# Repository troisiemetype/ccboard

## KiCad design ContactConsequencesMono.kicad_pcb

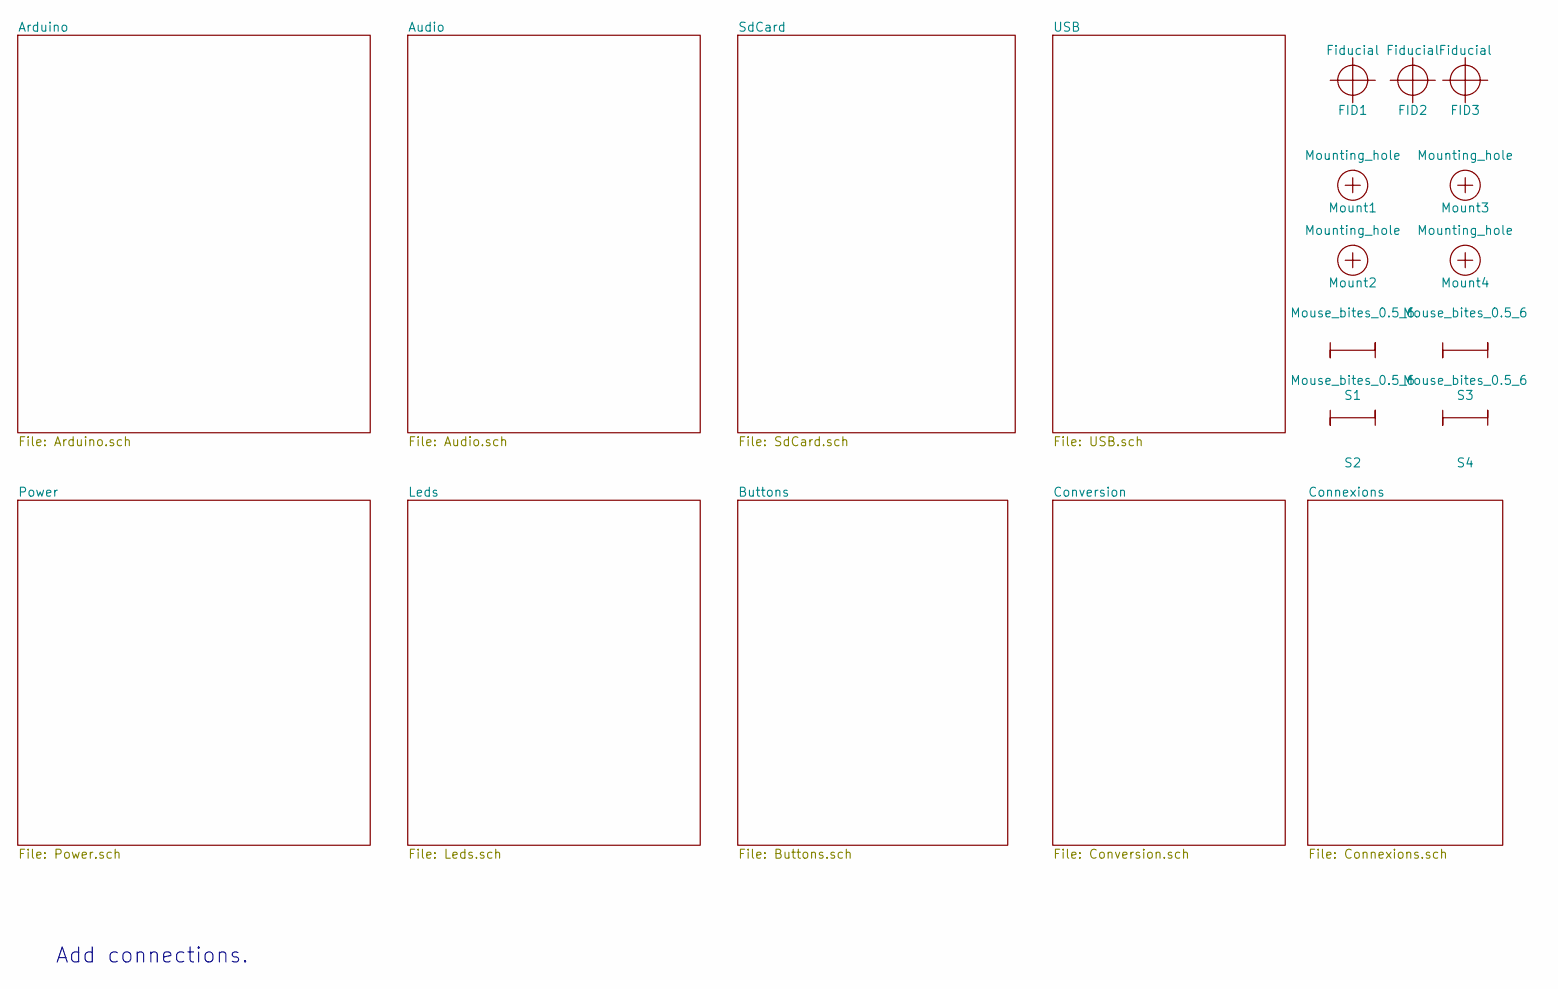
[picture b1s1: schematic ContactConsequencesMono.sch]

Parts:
FID1, FID2, FID3: Fiducial; Fiducial_1mm_Dia_2.54mm_Outer_CopperTop
Mount1, Mount2, Mount3, Mount4: Mounting_hole; MountingHole_3.2mm_M3
S1, S2, S3, S4: Mouse_bites_0.5_6

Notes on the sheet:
Add connections.

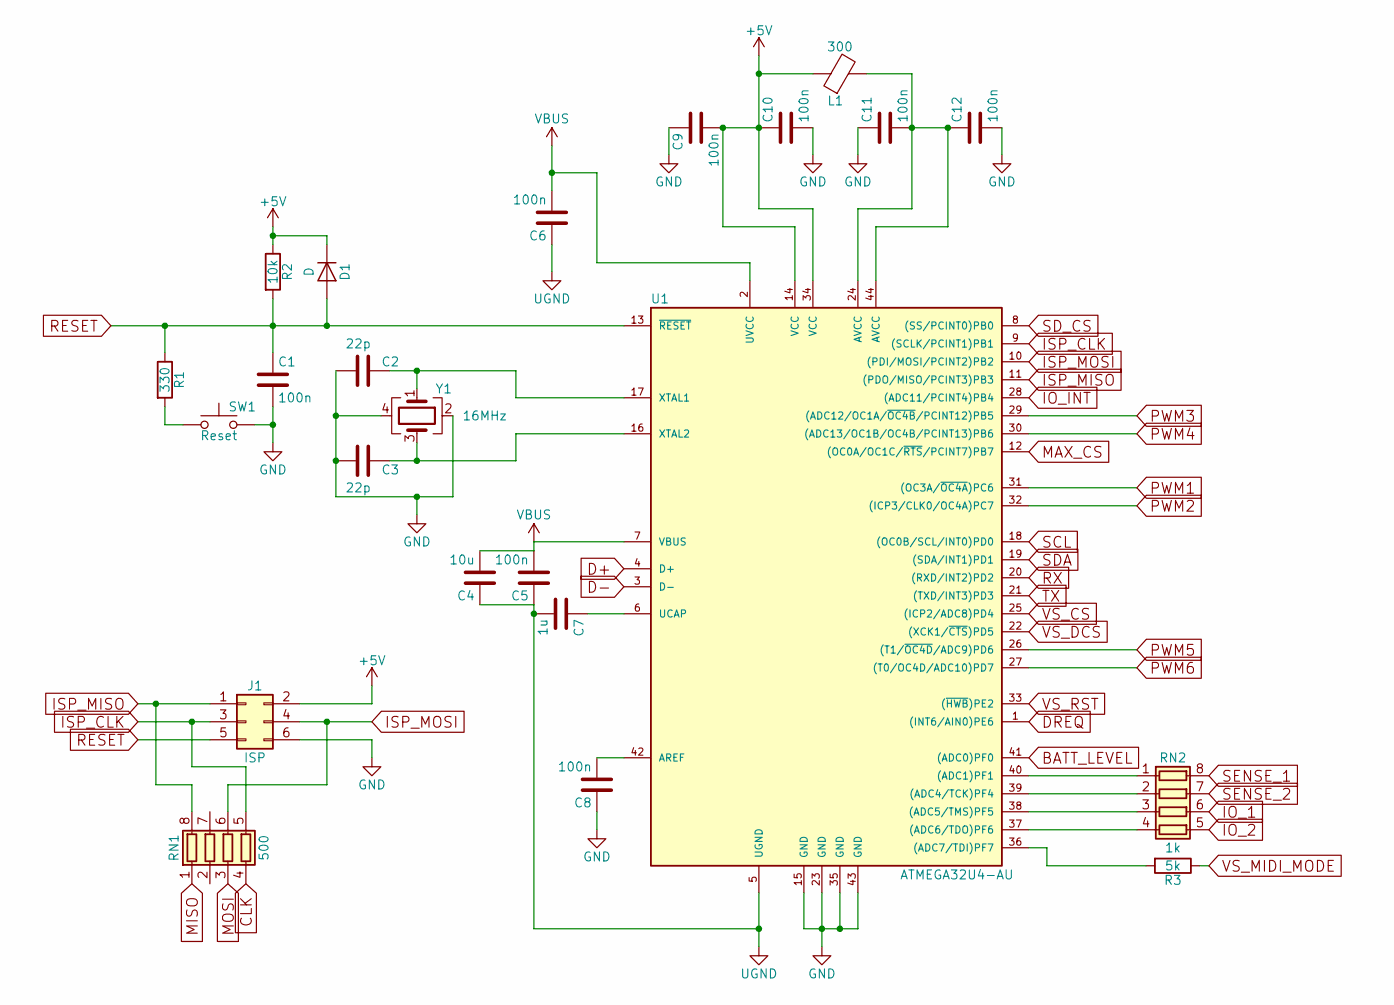
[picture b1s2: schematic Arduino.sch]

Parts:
C1, C5, C6, C8, C9, C10, C11, C12: 100n; C_0603
C2, C3: 22p; C_0603
C4: 10u; C_0603
C7: 1u; C_0603
D1: D; D_1206
J1: ISP; Pin_Header_Straight_2x03_Pitch2.54mm
L1: 300; L_0603
R1: 330; R_0603
R2: 10k; R_0603
R3: 5k; R_0603
RN1: 500; R_Array_Concave_4x0603
RN2: 1k; R_Array_Concave_4x0603
SW1: Reset; SW_Tactile_SKHH_Angled
U1: ATMEGA32U4-AU; TQFP-44_10x10mm_Pitch0.8mm
Y1: 16MHz; Crystal_SMD_5032-4pin_5.0x3.2mm

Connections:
+5V: C9.2, C10.1, D1.1 (K), J1.2, L1.1, R2.1, U1.14 (VCC), U1.34 (VCC); also elsewhere on the board
BATT_LEVEL: U1.41 ((ADC0)PF0); also elsewhere on the board
CLK: RN1.4 (R4.1); also elsewhere on the board
D+: U1.4 (D+); also elsewhere on the board
D-: U1.3 (D-); also elsewhere on the board
DGND: C1.2, C2.2, C3.2, C8.1, C9.1, C10.2, C11.1, C12.2, J1.6, SW1.2, U1.15 (GND), U1.23 (GND), U1.35 (GND), U1.43 (GND), Y1.2, Y1.4; also elsewhere on the board
DREQ: U1.1 ((INT6/AIN0)PE6); also elsewhere on the board
IO_1: RN2.6 (R3.2); also elsewhere on the board
IO_2: RN2.5 (R4.2); also elsewhere on the board
IO_INT: U1.28 ((ADC11/PCINT4)PB4); also elsewhere on the board
ISP_CLK: J1.3, RN1.5 (R4.2), U1.9 ((SCLK/PCINT1)PB1)
ISP_MISO: J1.1, RN1.8 (R1.2), U1.11 ((PDO/MISO/PCINT3)PB3)
ISP_MOSI: J1.4, RN1.6 (R3.2), U1.10 ((PDI/MOSI/PCINT2)PB2)
MAX_CS: U1.12 ((OC0A/OC1C/~RTS~/PCINT7)PB7); also elsewhere on the board
MISO: RN1.1 (R1.1); also elsewhere on the board
MOSI: RN1.3 (R3.1); also elsewhere on the board
unnamed: C2.1, U1.17 (XTAL1), Y1.1
unnamed: C3.1, U1.16 (XTAL2), Y1.3
unnamed: C7.1, U1.6 (UCAP)
unnamed: C8.2, U1.42 (AREF)
unnamed: C11.2, C12.1, L1.2, U1.24 (AVCC), U1.44 (AVCC)
unnamed: R1.2, SW1.1
unnamed: R3.2, U1.36 ((ADC7/TDI)PF7)
unnamed: RN2.1 (R1.1), U1.40 ((ADC1)PF1)
unnamed: RN2.2 (R2.1), U1.39 ((ADC4/TCK)PF4)
unnamed: RN2.3 (R3.1), U1.38 ((ADC5/TMS)PF5)
unnamed: RN2.4 (R4.1), U1.37 ((ADC6/TDO)PF6)
PWM1: U1.31 ((OC3A/~OC4A~)PC6); also elsewhere on the board
PWM2: U1.32 ((ICP3/CLK0/OC4A)PC7); also elsewhere on the board
PWM3: U1.29 ((ADC12/OC1A/~OC4B~/PCINT12)PB5); also elsewhere on the board
PWM4: U1.30 ((ADC13/OC1B/OC4B/PCINT13)PB6); also elsewhere on the board
PWM5: U1.26 ((T1/~OC4D~/ADC9)PD6); also elsewhere on the board
PWM6: U1.27 ((T0/OC4D/ADC10)PD7); also elsewhere on the board
RESET: C1.1, D1.2 (A), J1.5, R1.1, R2.2, U1.13 (~RESET~)
RX: U1.20 ((RXD/INT2)PD2); also elsewhere on the board
SCL: U1.18 ((OC0B/SCL/INT0)PD0); also elsewhere on the board
SDA: U1.19 ((SDA/INT1)PD1); also elsewhere on the board
SD_CS: U1.8 ((SS/PCINT0)PB0); also elsewhere on the board
SENSE_1: RN2.8 (R1.2); also elsewhere on the board
SENSE_2: RN2.7 (R2.2); also elsewhere on the board
TX: U1.21 ((TXD/INT3)PD3); also elsewhere on the board
UGND: C4.1, C5.1, C6.1, C7.2, U1.5 (UGND); also elsewhere on the board
VBUS: C4.2, C5.2, C6.2, U1.2 (UVCC), U1.7 (VBUS); also elsewhere on the board
VS_CS: U1.25 ((ICP2/ADC8)PD4); also elsewhere on the board
VS_DCS: U1.22 ((XCK1/~CTS~)PD5); also elsewhere on the board
VS_MIDI_MODE: R3.1; also elsewhere on the board
VS_RST: U1.33 ((~HWB~)PE2); also elsewhere on the board

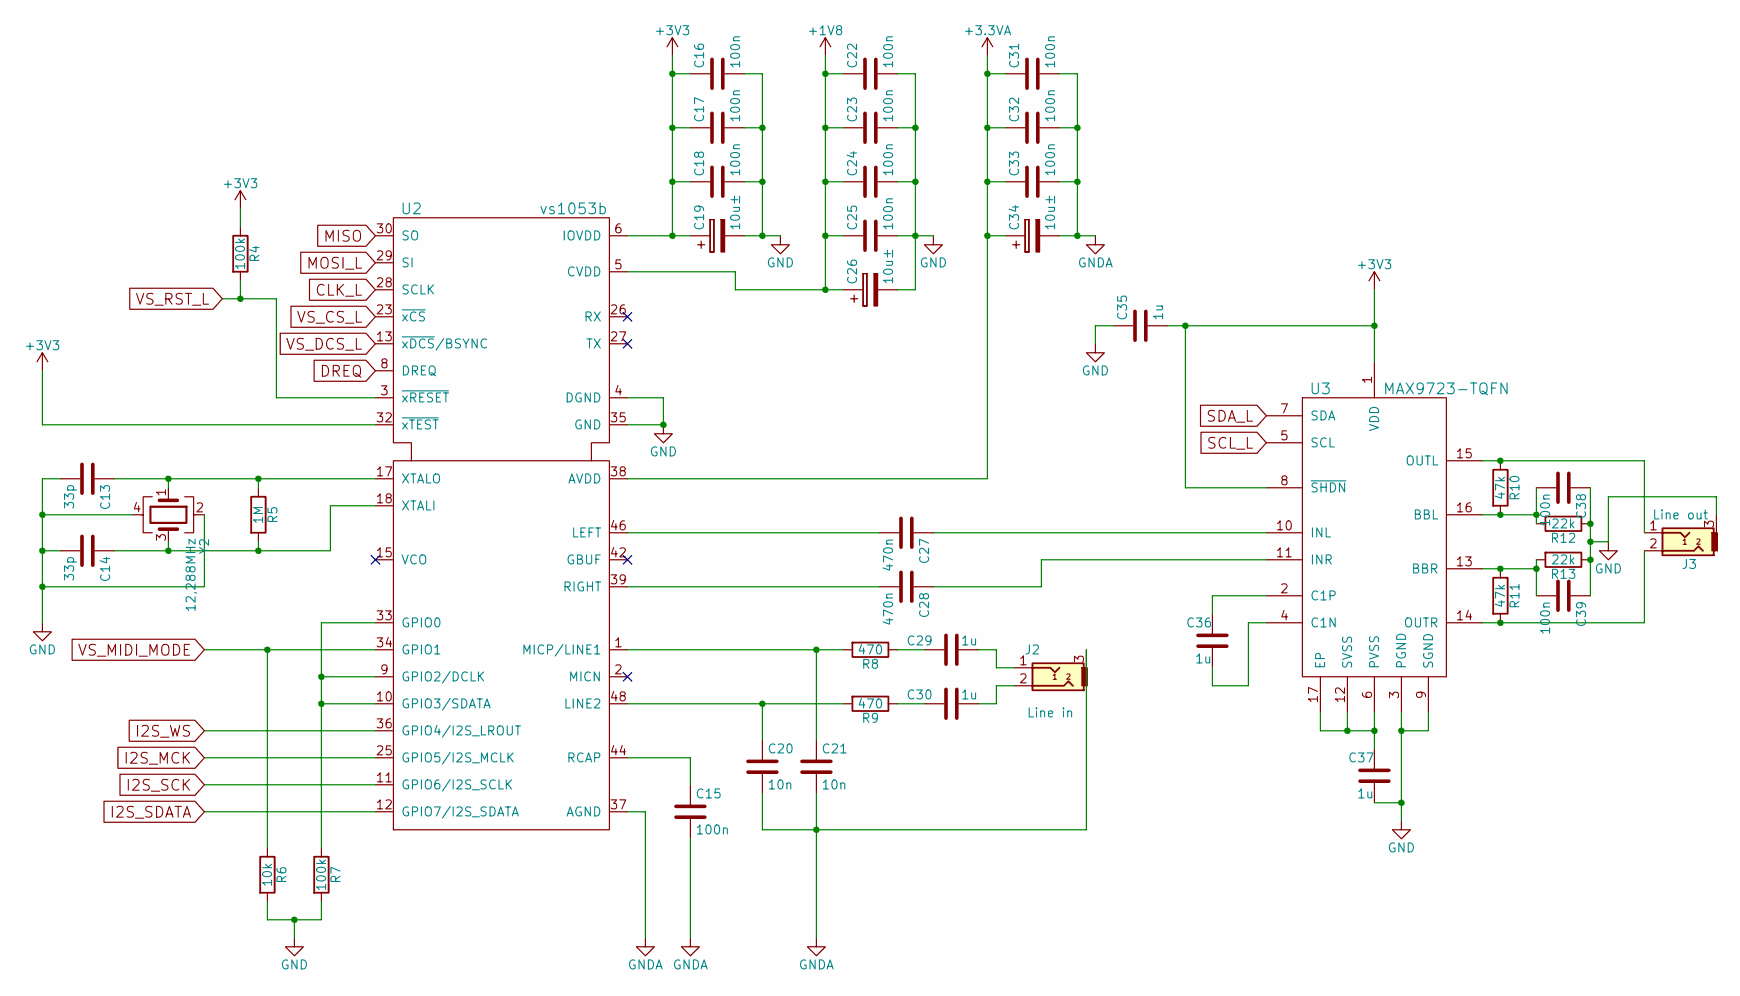
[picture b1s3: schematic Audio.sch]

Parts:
C13, C14: 33p; C_0603
C15, C16, C17, C18, C22, C23, C24, C25, C31, C32, C33, C38, C39: 100n; C_0603
C19, C26, C34: 10u±; CP_Tantalum_Case-A_EIA-3216-18_Reflow
C20, C21: 10n; C_0603
C27, C28: 470n; C_0603
C29, C30, C35, C36, C37: 1u; C_0603
J2: Line in; PJ320D_3.5mm_Jack
J3: Line out; PJ320D_3.5mm_Jack
R4, R7: 100k; R_0603
R5: 1M; R_0603
R6: 10k; R_0603
R8, R9: 470; R_0603
R10, R11: 47k; R_0603
R12, R13: 22k; R_0603
U2: vs1053b; LQFP-48_7x7mm_Pitch0.5mm
U3: MAX9723-TQFN; QFN-16-1EP_4x4mm_Pitch0.65mm
Y2: 12,288MHz; Crystal_SMD_5032-4pin_5.0x3.2mm

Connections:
+1V8: C22.1, C23.1, C24.1, C25.1, C26.1, U2.5 (CVDD), U2.7 (CVDD), U2.24 (CVDD), U2.31 (CVDD); also elsewhere on the board
+3.3VA: C31.1, C32.1, C33.1, C34.1, U2.38 (AVDD), U2.43 (AVDD), U2.45 (AVDD); also elsewhere on the board
AGND: C15.2, C20.2, C21.2, C31.2, C32.2, C33.2, C34.2, J2.3, U2.37 (AGND), U2.40 (AGND), U2.41 (AGND), U2.47 (AGND); also elsewhere on the board
CLK_L: U2.28 (SCLK); also elsewhere on the board
DGND: C13.2, C14.2, C16.2, C17.2, C18.2, C19.2, C22.2, C23.2, C24.2, C25.2, C26.2, C35.1, C37.2, C38.1, C39.1, J3.3, R6.2, R7.2, R12.1, R13.1, U2.4 (DGND), U2.16 (DGND), U2.20 (DGND), U2.21 (DGND), U2.22 (DGND), U2.35 (GND), U3.3 (PGND), U3.9 (SGND), Y2.2, Y2.4; also elsewhere on the board
DREQ: U2.8 (DREQ); also elsewhere on the board
I2S_MCK: U2.25 (GPIO5/I2S_MCLK); also elsewhere on the board
I2S_SCK: U2.11 (GPIO6/I2S_SCLK); also elsewhere on the board
I2S_SDATA: U2.12 (GPIO7/I2S_SDATA); also elsewhere on the board
I2S_WS: U2.36 (GPIO4/I2S_LROUT); also elsewhere on the board
MISO: U2.30 (SO); also elsewhere on the board
MOSI_L: U2.29 (SI); also elsewhere on the board
unnamed: C13.1, R5.1, U2.17 (XTALO), Y2.1
unnamed: C14.1, R5.2, U2.18 (XTALI), Y2.3
unnamed: C15.1, U2.44 (RCAP)
unnamed: C20.1, R9.2, U2.48 (LINE2)
unnamed: C21.1, R8.2, U2.1 (MICP/LINE1)
unnamed: C27.1, U3.10 (INL)
unnamed: C27.2, U2.46 (LEFT)
unnamed: C28.1, U3.11 (INR)
unnamed: C28.2, U2.39 (RIGHT)
unnamed: C29.1, R8.1
unnamed: C29.2, J2.1
unnamed: C30.1, R9.1
unnamed: C30.2, J2.2
unnamed: C36.1, U3.2 (C1P)
unnamed: C36.2, U3.4 (C1N)
unnamed: C37.1, U3.6 (PVSS), U3.12 (SVSS), U3.17 (EP)
unnamed: C38.2, R10.2, R12.2, U3.16 (BBL)
unnamed: C39.2, R11.1, R13.2, U3.13 (BBR)
unnamed: J3.1, R10.1, U3.15 (OUTL)
unnamed: J3.2, R11.2, U3.14 (OUTR)
unnamed: R7.1, U2.9 (GPIO2/DCLK), U2.10 (GPIO3/SDATA), U2.33 (GPIO0)
SCL_L: U3.5 (SCL); also elsewhere on the board
SDA_L: U3.7 (SDA); also elsewhere on the board
VS_CS_L: U2.23 (~xCS); also elsewhere on the board
VS_DCS_L: U2.13 (~xDCS~/BSYNC); also elsewhere on the board
VS_MIDI_MODE: R6.1, U2.34 (GPIO1); also elsewhere on the board
VS_RST_L: R4.2, U2.3 (~xRESET); also elsewhere on the board

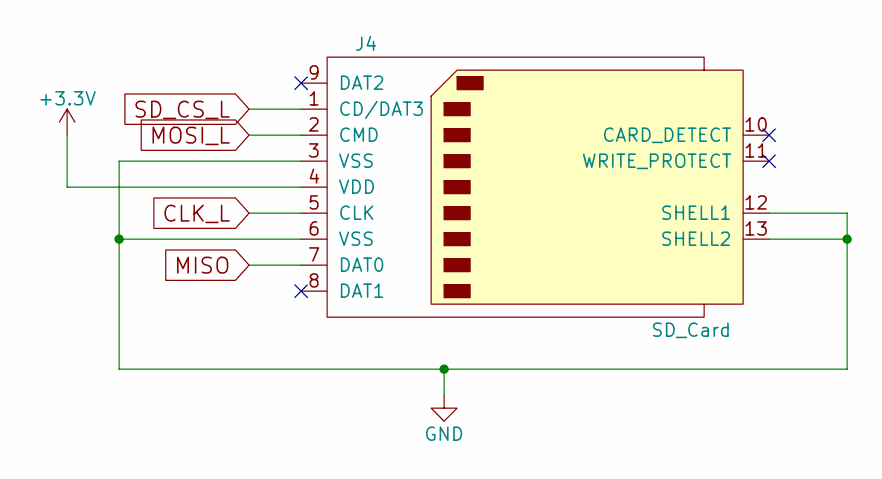
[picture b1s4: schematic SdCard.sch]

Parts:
J4: SD_Card; SD_Card_Receptacle

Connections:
CLK_L: J4.5 (CLK); also elsewhere on the board
DGND: J4.3 (VSS), J4.6 (VSS), J4.12 (SHELL1), J4.13 (SHELL2); also elsewhere on the board
MISO: J4.7 (DAT0); also elsewhere on the board
MOSI_L: J4.2 (CMD); also elsewhere on the board
SD_CS_L: J4.1 (CD/DAT3); also elsewhere on the board

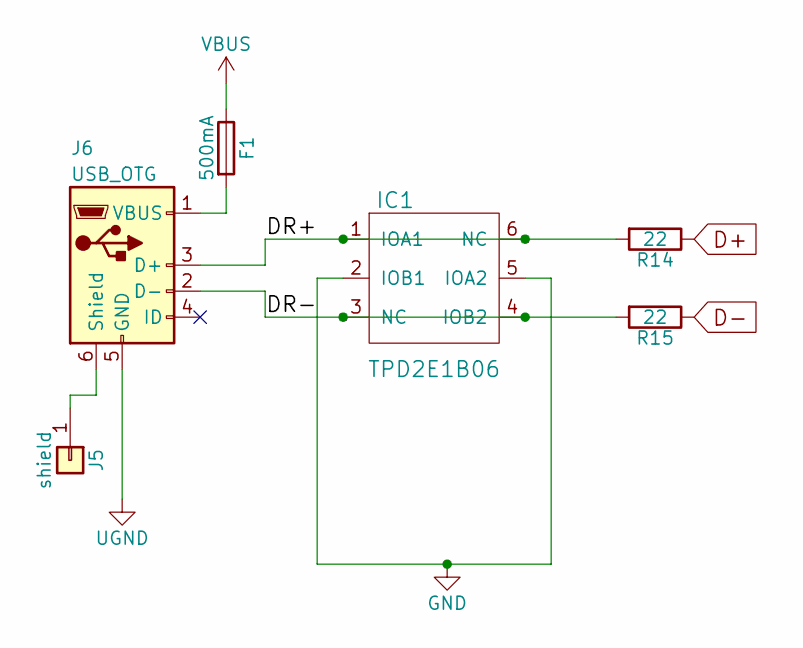
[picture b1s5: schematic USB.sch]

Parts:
F1: 500mA; Fuse_SMD1206_Reflow
IC1: TPD2E1B06; SOT-5X3
J5: shield; Pin_Header_Straight_1x01_Pitch2.54mm
J6: USB_OTG; USB_Micro-B
R14, R15: 22; R_0603

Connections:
/USB/DR+: IC1.1 (IOA1), IC1.6 (NC), J6.3 (D+), R14.2
/USB/DR-: IC1.3 (NC), IC1.4 (IOB2), J6.2 (D-), R15.2
D+: R14.1; also elsewhere on the board
D-: R15.1; also elsewhere on the board
DGND: IC1.2 (IOB1), IC1.5 (IOA2); also elsewhere on the board
unnamed: F1.2, J6.1 (VBUS)
unnamed: J5.1, J6.6 (Shield)
UGND: J6.5 (GND); also elsewhere on the board
VBUS: F1.1; also elsewhere on the board

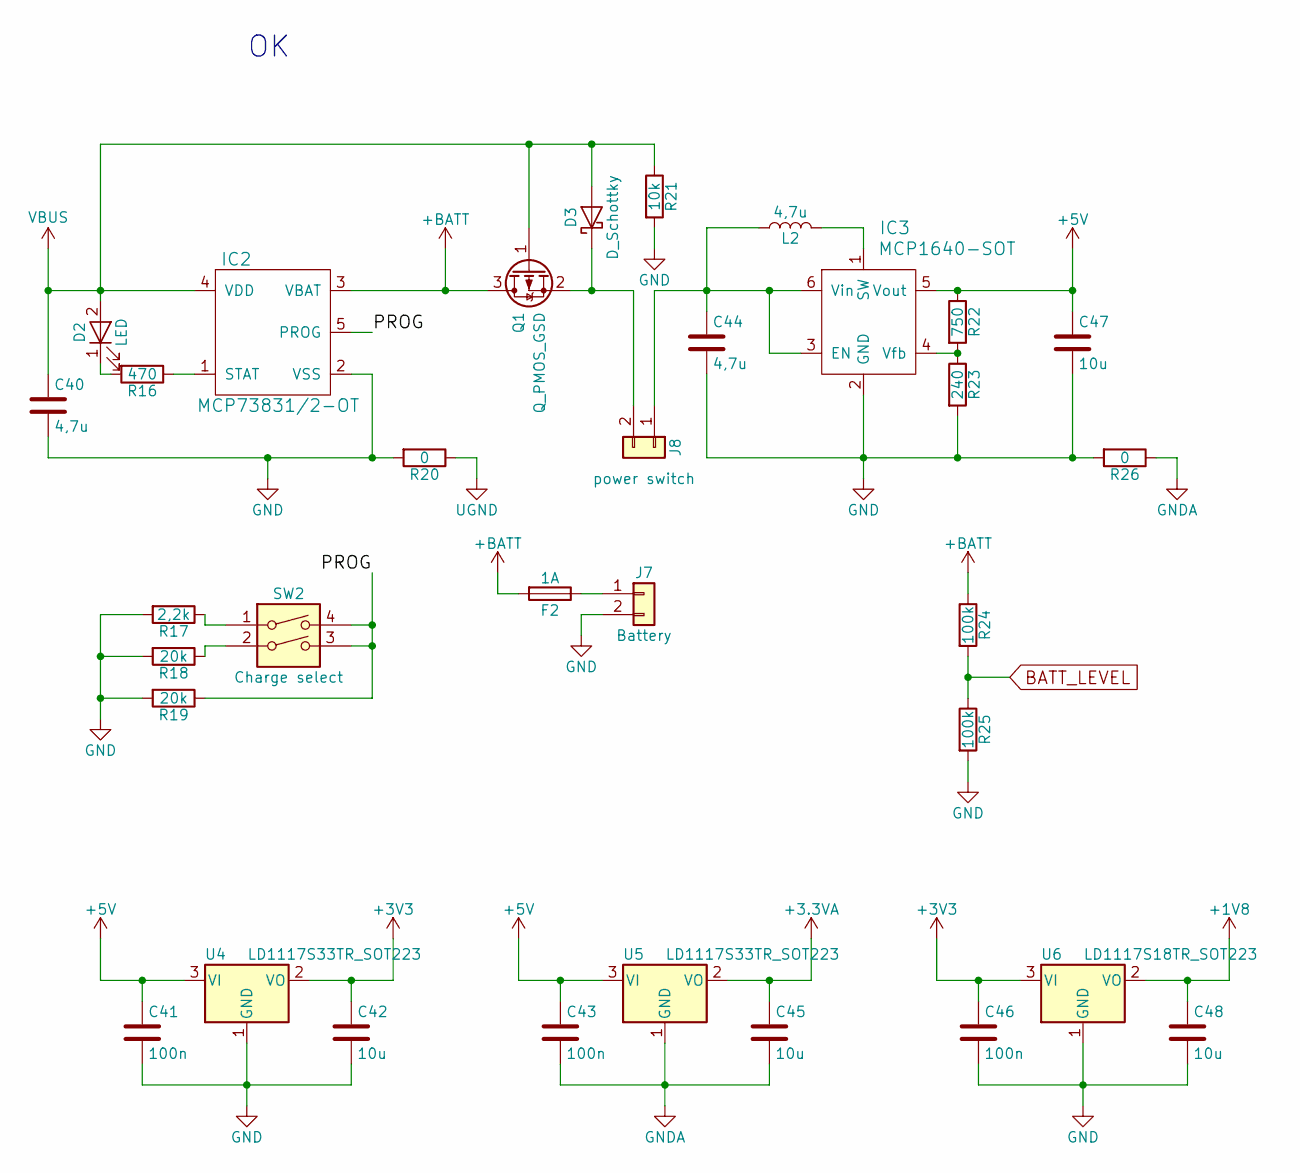
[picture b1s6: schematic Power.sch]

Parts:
C40, C44: 4,7u; C_0603
C41, C43, C46: 100n; C_0603
C42, C45, C47, C48: 10u; C_0603
D2: LED; LED_0603
D3: D_Schottky; D_SOD-123
F2: 1A; Fuse_SMD1206_Reflow
IC2: MCP73831/2-OT; SOT-23-5
IC3: MCP1640-SOT; SOT-23-6
J7: Battery; JST_PH_S2B-PH-SM4-TB_02x2.00mm_Angled
J8: power switch; Pin_Header_Straight_1x02_Pitch2.54mm
L2: 4,7u; L_Vishay_IHLP-1616
Q1: Q_PMOS_GSD; SOT-23
R16: 470; R_0603
R17: 2,2k; R_0603
R18, R19: 20k; R_0603
R20, R26: 0; R_0603
R21: 10k; R_0603
R22: 750; R_0603
R23: 240; R_0603
R24, R25: 100k; R_0603
SW2: Charge select; SW_DIP_x2_W5.08mm_Slide_Copal_CHS-A
U4, U5: LD1117S33TR_SOT223; SOT-223-3_TabPin2
U6: LD1117S18TR_SOT223; SOT-223-3_TabPin2

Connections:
+1V8: C48.1, U6.2 (VO); also elsewhere on the board
+3.3VA: C45.1, U5.2 (VO); also elsewhere on the board
+5V: C41.1, C43.1, C47.1, IC3.5 (Vout), R22.1, U4.3 (VI), U5.3 (VI); also elsewhere on the board
+BATT: F2.2, IC2.3 (VBAT), Q1.3 (D), R24.1
/Power/PROG: IC2.5 (PROG), R19.1, SW2.3, SW2.4
AGND: C43.2, C45.2, R26.1, U5.1 (GND); also elsewhere on the board
BATT_LEVEL: R24.2, R25.1; also elsewhere on the board
DGND: C40.2, C41.2, C42.2, C44.2, C46.2, C47.2, C48.2, IC2.2 (VSS), IC3.2 (GND), J7.2, R17.2, R18.2, R19.2, R20.2, R21.2, R23.2, R25.2, R26.2, U4.1 (GND), U6.1 (GND); also elsewhere on the board
unnamed: C44.1, IC3.3 (EN), IC3.6 (Vin), J8.1, L2.1
unnamed: D2.1 (K), R16.2
unnamed: D3.1 (K), J8.2, Q1.2 (S)
unnamed: F2.1, J7.1
unnamed: IC2.1 (STAT), R16.1
unnamed: IC3.1 (SW), L2.2
unnamed: IC3.4 (Vfb), R22.2, R23.1
unnamed: R17.1, SW2.1
unnamed: R18.1, SW2.2
UGND: R20.1; also elsewhere on the board
VBUS: C40.1, D2.2 (A), D3.2 (A), IC2.4 (VDD), Q1.1 (G), R21.1; also elsewhere on the board

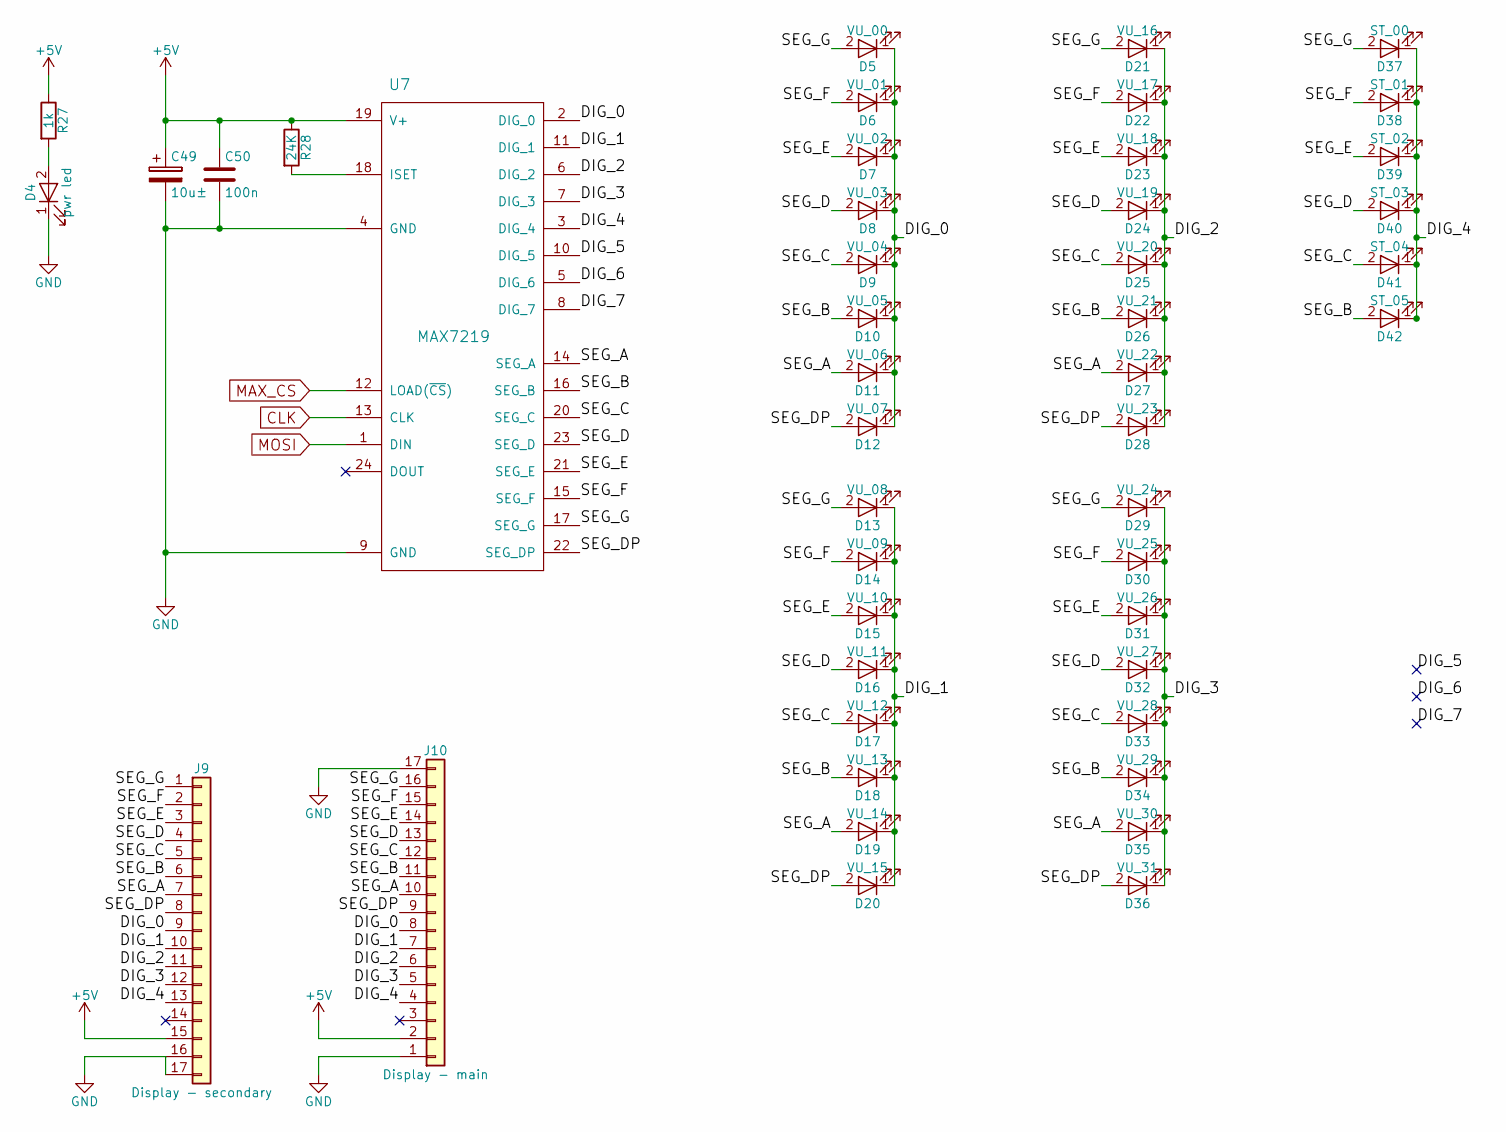
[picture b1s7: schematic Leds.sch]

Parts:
C49: 10u±; CP_Tantalum_Case-A_EIA-3216-18_Reflow
C50: 100n; C_0603
D4: pwr led; LED_0603
D5: VU_00; LED_0603
D6: VU_01; LED_0603
D7: VU_02; LED_0603
D8: VU_03; LED_0603
D9: VU_04; LED_0603
D10: VU_05; LED_0603
D11: VU_06; LED_0603
D12: VU_07; LED_0603
D13: VU_08; LED_0603
D14: VU_09; LED_0603
D15: VU_10; LED_0603
D16: VU_11; LED_0603
D17: VU_12; LED_0603
D18: VU_13; LED_0603
D19: VU_14; LED_0603
D20: VU_15; LED_0603
D21: VU_16; LED_0603
D22: VU_17; LED_0603
D23: VU_18; LED_0603
D24: VU_19; LED_0603
D25: VU_20; LED_0603
D26: VU_21; LED_0603
D27: VU_22; LED_0603
D28: VU_23; LED_0603
D29: VU_24; LED_0603
D30: VU_25; LED_0603
D31: VU_26; LED_0603
D32: VU_27; LED_0603
D33: VU_28; LED_0603
D34: VU_29; LED_0603
D35: VU_30; LED_0603
D36: VU_31; LED_0603
D37: ST_00; LED_0603
D38: ST_01; LED_0603
D39: ST_02; LED_0603
D40: ST_03; LED_0603
D41: ST_04; LED_0603
D42: ST_05; LED_0603
J9: Display - secondary; Hirose_FH12-16S-1_SH
J10: Display - main; Hirose_FH12-16S-1_SH
R27: 1k; R_0603
R28: 24K; R_0603
U7: MAX7219; SOIC-24W_7.5x15.4mm_Pitch1.27mm

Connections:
+5V: C49.1, C50.1, J9.15, J10.2, R27.1, R28.1, U7.19 (V+); also elsewhere on the board
/Leds/DIG_0: D5.1 (K), D6.1 (K), D7.1 (K), D8.1 (K), D9.1 (K), D10.1 (K), D11.1 (K), D12.1 (K), J9.9, J10.8, U7.2 (DIG_0)
/Leds/DIG_1: D13.1 (K), D14.1 (K), D15.1 (K), D16.1 (K), D17.1 (K), D18.1 (K), D19.1 (K), D20.1 (K), J9.10, J10.7, U7.11 (DIG_1)
/Leds/DIG_2: D21.1 (K), D22.1 (K), D23.1 (K), D24.1 (K), D25.1 (K), D26.1 (K), D27.1 (K), D28.1 (K), J9.11, J10.6, U7.6 (DIG_2)
/Leds/DIG_3: D29.1 (K), D30.1 (K), D31.1 (K), D32.1 (K), D33.1 (K), D34.1 (K), D35.1 (K), D36.1 (K), J9.12, J10.5, U7.7 (DIG_3)
/Leds/DIG_4: D37.1 (K), D38.1 (K), D39.1 (K), D40.1 (K), D41.1 (K), D42.1 (K), J9.13, J10.4, U7.3 (DIG_4)
/Leds/DIG_5: U7.10 (DIG_5)
/Leds/DIG_6: U7.5 (DIG_6)
/Leds/DIG_7: U7.8 (DIG_7)
/Leds/SEG_A: D11.2 (A), D19.2 (A), D27.2 (A), D35.2 (A), J9.7, J10.10, U7.14 (SEG_A)
/Leds/SEG_B: D10.2 (A), D18.2 (A), D26.2 (A), D34.2 (A), D42.2 (A), J9.6, J10.11, U7.16 (SEG_B)
/Leds/SEG_C: D9.2 (A), D17.2 (A), D25.2 (A), D33.2 (A), D41.2 (A), J9.5, J10.12, U7.20 (SEG_C)
/Leds/SEG_D: D8.2 (A), D16.2 (A), D24.2 (A), D32.2 (A), D40.2 (A), J9.4, J10.13, U7.23 (SEG_D)
/Leds/SEG_DP: D12.2 (A), D20.2 (A), D28.2 (A), D36.2 (A), J9.8, J10.9, U7.22 (SEG_DP)
/Leds/SEG_E: D7.2 (A), D15.2 (A), D23.2 (A), D31.2 (A), D39.2 (A), J9.3, J10.14, U7.21 (SEG_E)
/Leds/SEG_F: D6.2 (A), D14.2 (A), D22.2 (A), D30.2 (A), D38.2 (A), J9.2, J10.15, U7.15 (SEG_F)
/Leds/SEG_G: D5.2 (A), D13.2 (A), D21.2 (A), D29.2 (A), D37.2 (A), J9.1, J10.16, U7.17 (SEG_G)
CLK: U7.13 (CLK); also elsewhere on the board
DGND: C49.2, C50.2, D4.1 (K), J9.16, J9.17, J10.1, J10.17, U7.4 (GND), U7.9 (GND); also elsewhere on the board
MAX_CS: U7.12 (LOAD(~CS~)); also elsewhere on the board
MOSI: U7.1 (DIN); also elsewhere on the board
unnamed: D4.2 (A), R27.2
unnamed: R28.2, U7.18 (ISET)

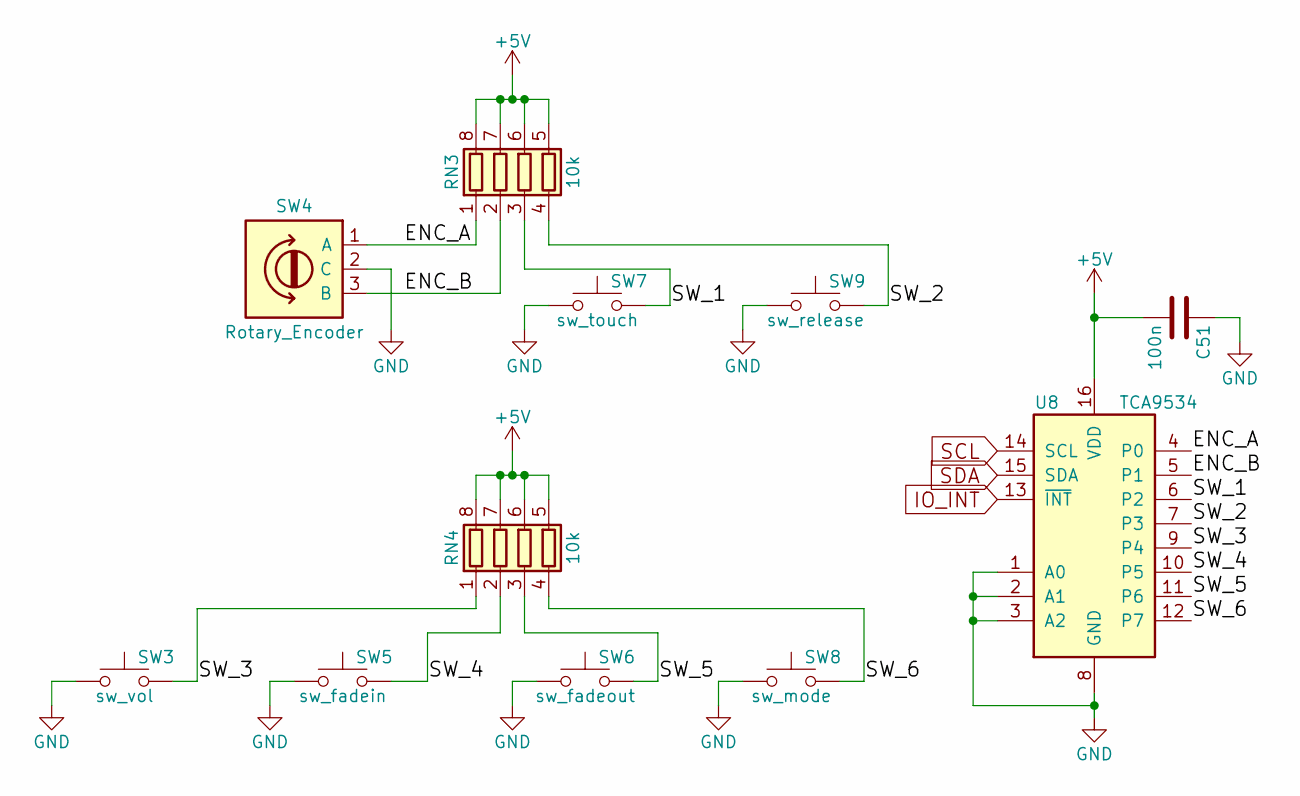
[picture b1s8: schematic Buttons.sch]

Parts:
C51: 100n; C_0603
RN3, RN4: 10k; R_Array_Concave_4x0603
SW3: sw_vol; SW_Tactile_SKHH_Angled
SW4: Rotary_Encoder; ALPS_EC11B_rotary_encoder
SW5: sw_fadein; SW_Tactile_SKHH_Angled
SW6: sw_fadeout; SW_Tactile_SKHH_Angled
SW7: sw_touch; SW_Tactile_SKHH_Angled
SW8: sw_mode; SW_Tactile_SKHH_Angled
SW9: sw_release; SW_Tactile_SKHH_Angled
U8: TCA9534; TSSOP-16_4.4x5mm_Pitch0.65mm

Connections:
+5V: C51.2, RN3.5 (R4.2), RN3.6 (R3.2), RN3.7 (R2.2), RN3.8 (R1.2), RN4.5 (R4.2), RN4.6 (R3.2), RN4.7 (R2.2), RN4.8 (R1.2), U8.16 (VDD); also elsewhere on the board
/Buttons/ENC_A: RN3.1 (R1.1), SW4.1 (A), U8.4 (P0)
/Buttons/ENC_B: RN3.2 (R2.1), SW4.3 (B), U8.5 (P1)
/Buttons/SW_1: RN3.3 (R3.1), SW7.2, U8.6 (P2)
/Buttons/SW_2: RN3.4 (R4.1), SW9.2, U8.7 (P3)
/Buttons/SW_3: RN4.1 (R1.1), SW3.2, U8.9 (P4)
/Buttons/SW_4: RN4.2 (R2.1), SW5.2, U8.10 (P5)
/Buttons/SW_5: RN4.3 (R3.1), SW6.2, U8.11 (P6)
/Buttons/SW_6: RN4.4 (R4.1), SW8.2, U8.12 (P7)
DGND: C51.1, SW3.1, SW4.2 (C), SW5.1, SW6.1, SW7.1, SW8.1, SW9.1, U8.1 (A0), U8.2 (A1), U8.3 (A2), U8.8 (GND); also elsewhere on the board
IO_INT: U8.13 (~INT~); also elsewhere on the board
SCL: U8.14 (SCL); also elsewhere on the board
SDA: U8.15 (SDA); also elsewhere on the board

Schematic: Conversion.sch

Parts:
C52, C53: 100n; C_0603
U9: TXS0108EPWR; TSSOP-20_4.4x6.5mm_Pitch0.65mm

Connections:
+5V: C53.2, U9.19 (VCCB); also elsewhere on the board
CLK: U9.16 (B4); also elsewhere on the board
CLK_L: U9.4 (A4); also elsewhere on the board
DGND: C52.2, C53.1, U9.11 (GND); also elsewhere on the board
MOSI: U9.17 (B3); also elsewhere on the board
MOSI_L: U9.3 (A3); also elsewhere on the board
SCL: U9.18 (B2); also elsewhere on the board
SCL_L: U9.2 (A2); also elsewhere on the board
SDA: U9.20 (B1); also elsewhere on the board
SDA_L: U9.1 (A1); also elsewhere on the board
SD_CS: U9.13 (B7); also elsewhere on the board
SD_CS_L: U9.9 (A7); also elsewhere on the board
VS_CS: U9.15 (B5); also elsewhere on the board
VS_CS_L: U9.7 (A5); also elsewhere on the board
VS_DCS: U9.14 (B6); also elsewhere on the board
VS_DCS_L: U9.8 (A6); also elsewhere on the board
VS_RST: U9.12 (B8); also elsewhere on the board
VS_RST_L: U9.10 (A8); also elsewhere on the board

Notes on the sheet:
Niveaux SPI, I2C.

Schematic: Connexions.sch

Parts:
J11: PWM; Pin_Header_Straight_1x08_Pitch2.54mm
J12: Sense1; PJ320D_3.5mm_Jack
J13: Sense2; PJ320D_3.5mm_Jack
J14: IO1; PJ320D_3.5mm_Jack
J15: IO2; PJ320D_3.5mm_Jack
J16: I2C; Pin_Header_Straight_1x04_Pitch2.54mm
J17: Serial; Pin_Header_Straight_1x04_Pitch2.54mm
J18: I2S; Pin_Header_Straight_1x06_Pitch2.54mm

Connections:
+5V: J11.7, J16.3, J17.3; also elsewhere on the board
DGND: J11.8, J12.2, J12.3, J12.4, J13.2, J13.3, J13.4, J14.2, J14.3, J14.4, J15.2, J15.3, J15.4, J16.4, J17.4, J18.6; also elsewhere on the board
I2S_MCK: J18.4; also elsewhere on the board
I2S_SCK: J18.3; also elsewhere on the board
I2S_SDATA: J18.2; also elsewhere on the board
I2S_WS: J18.1; also elsewhere on the board
IO_1: J14.1; also elsewhere on the board
IO_2: J15.1; also elsewhere on the board
PWM1: J11.2; also elsewhere on the board
PWM2: J11.1; also elsewhere on the board
PWM3: J11.4; also elsewhere on the board
PWM4: J11.3; also elsewhere on the board
PWM5: J11.6; also elsewhere on the board
PWM6: J11.5; also elsewhere on the board
RX: J17.1; also elsewhere on the board
SCL: J16.2; also elsewhere on the board
SDA: J16.1; also elsewhere on the board
SENSE_1: J12.1; also elsewhere on the board
SENSE_2: J13.1; also elsewhere on the board
TX: J17.2; also elsewhere on the board

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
